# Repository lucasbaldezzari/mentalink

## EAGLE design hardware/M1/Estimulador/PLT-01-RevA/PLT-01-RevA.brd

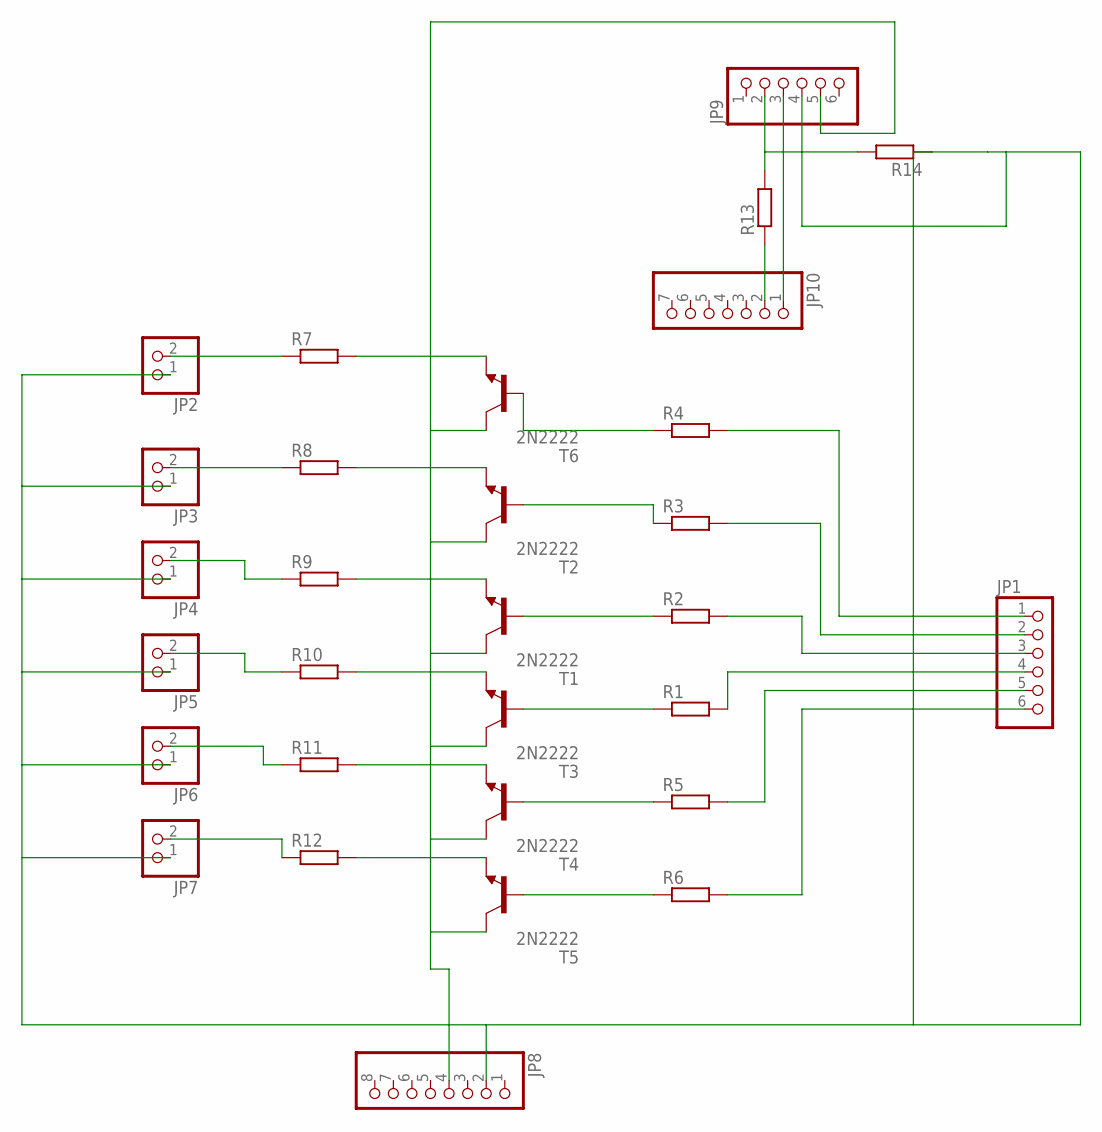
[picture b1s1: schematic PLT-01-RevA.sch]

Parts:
JP1, JP9: PINHD-1X6; 1X06
JP2, JP3, JP4, JP5, JP6, JP7: PINHD-1X2; 1X02
JP8: PINHD-1X8; 1X08
JP10: PINHD-1X7; 1X07
R1, R2, R3, R4, R5, R6, R7, R8, R9, R10, R11, R12, R13, R14: R-EU_0207/10; 0207/10
T1, T2, T3, T4, T5, T6: 2N2222; TO18

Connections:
GND: JP2.1, JP3.1, JP4.1, JP5.1, JP6.1, JP8.2, JP9.4, R14.1
unnamed: JP1.1, R4.2
unnamed: JP1.2, R3.2
unnamed: JP1.3, R2.2
unnamed: JP1.4, R1.2
unnamed: JP1.5, R5.2
unnamed: JP1.6, R6.2
unnamed: R6.1, T5.2 (B)
unnamed: R5.1, T4.2 (B)
unnamed: R1.1, T3.2 (B)
unnamed: R2.1, T1.2 (B)
unnamed: R3.1, T2.2 (B)
unnamed: R4.1, T6.2 (B)
unnamed: R7.2, T6.1 (E)
unnamed: JP2.2, R7.1
unnamed: R8.2, T2.1 (E)
unnamed: JP3.2, R8.1
unnamed: R9.2, T1.1 (E)
unnamed: JP4.2, R9.1
unnamed: R10.2, T3.1 (E)
unnamed: JP5.2, R10.1
unnamed: R11.2, T4.1 (E)
unnamed: JP6.2, R11.1
unnamed: R12.2, T5.1 (E)
unnamed: JP7.2, R12.1
unnamed: JP10.2, R13.1
unnamed: JP9.2, R13.2, R14.2
unnamed: JP9.3, JP10.1
unnamed: JP8.4, JP9.5, T1.3 (C), T2.3 (C), T3.3 (C), T4.3 (C), T5.3 (C), T6.3 (C)

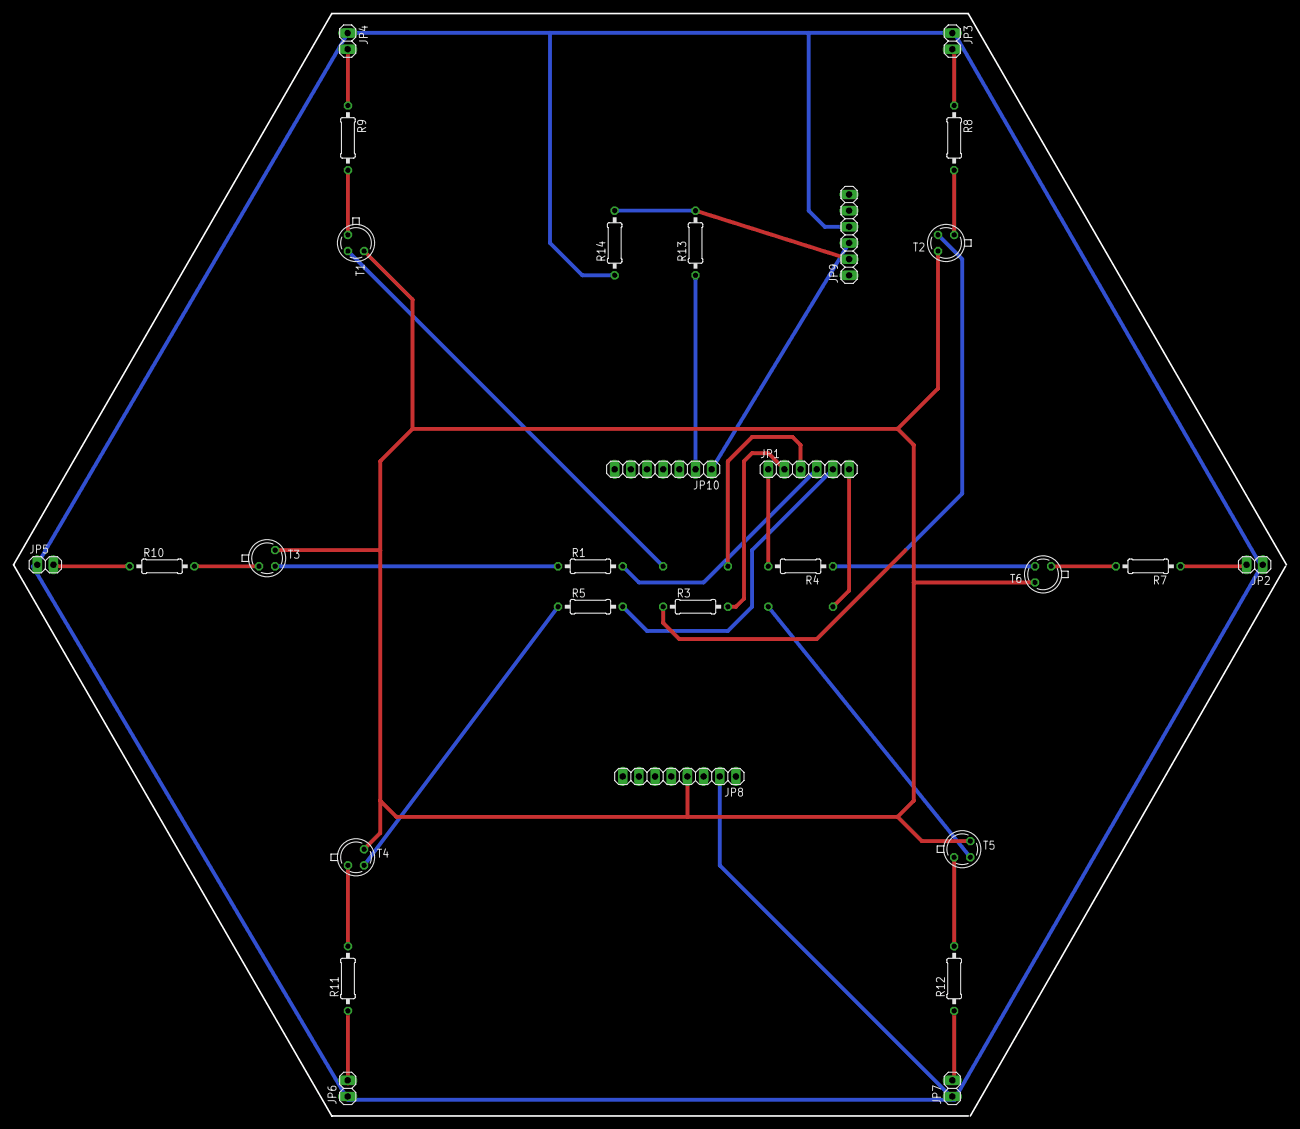
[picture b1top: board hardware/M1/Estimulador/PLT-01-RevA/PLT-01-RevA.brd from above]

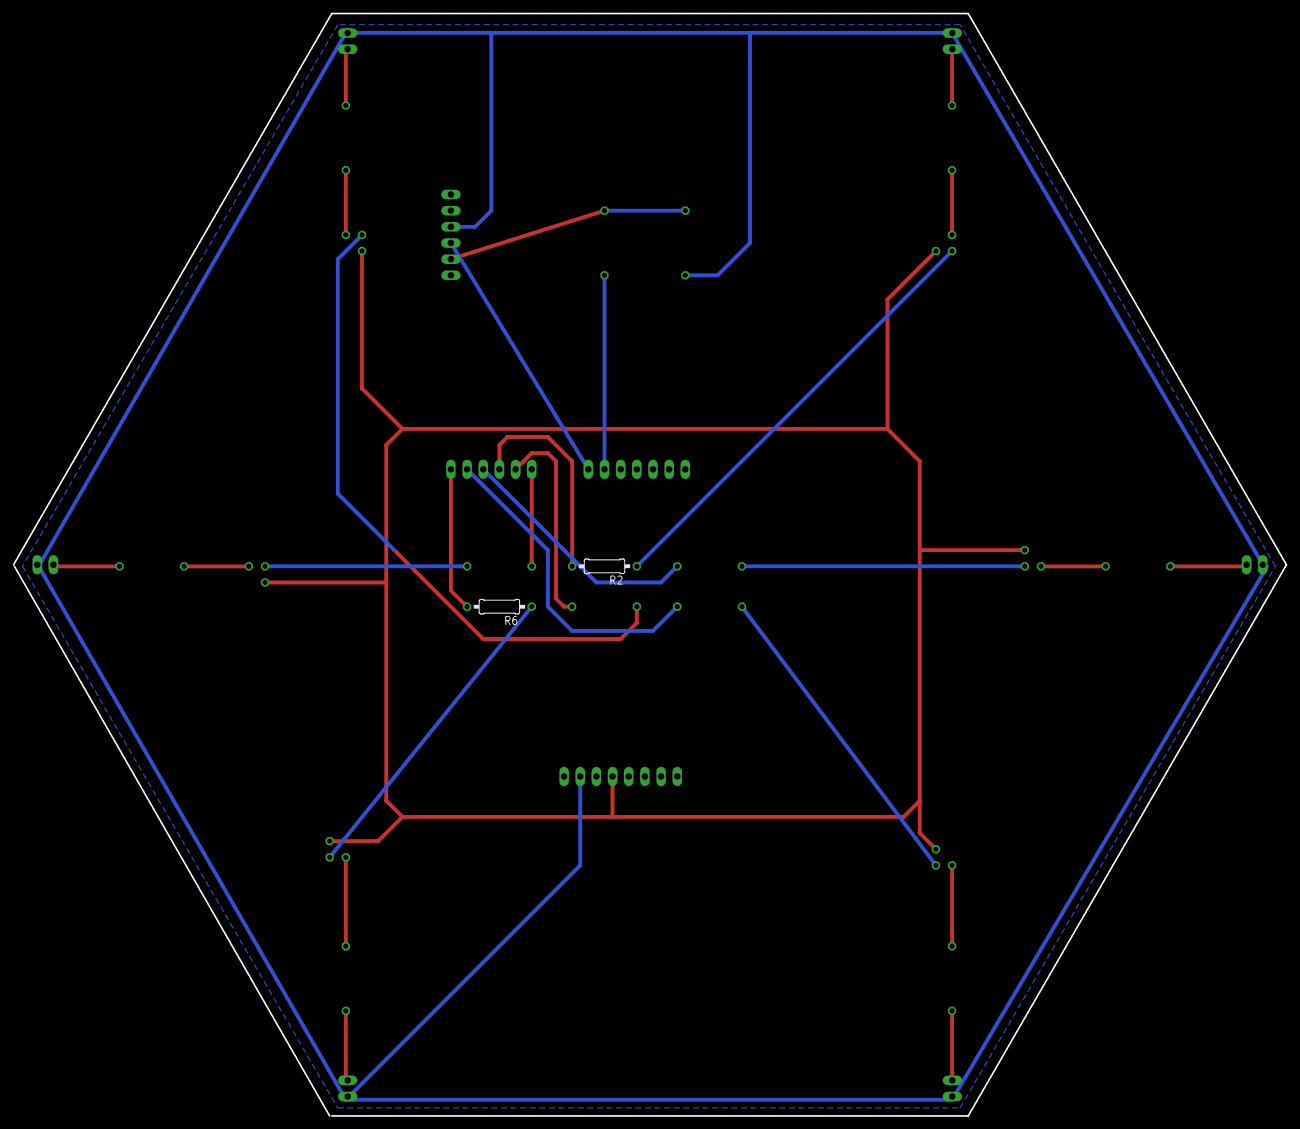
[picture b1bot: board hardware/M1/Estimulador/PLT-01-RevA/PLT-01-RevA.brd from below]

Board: 2 copper layers, 200.0 x 173.2 mm, 30 parts (2 on the bottom side), 29 nets.

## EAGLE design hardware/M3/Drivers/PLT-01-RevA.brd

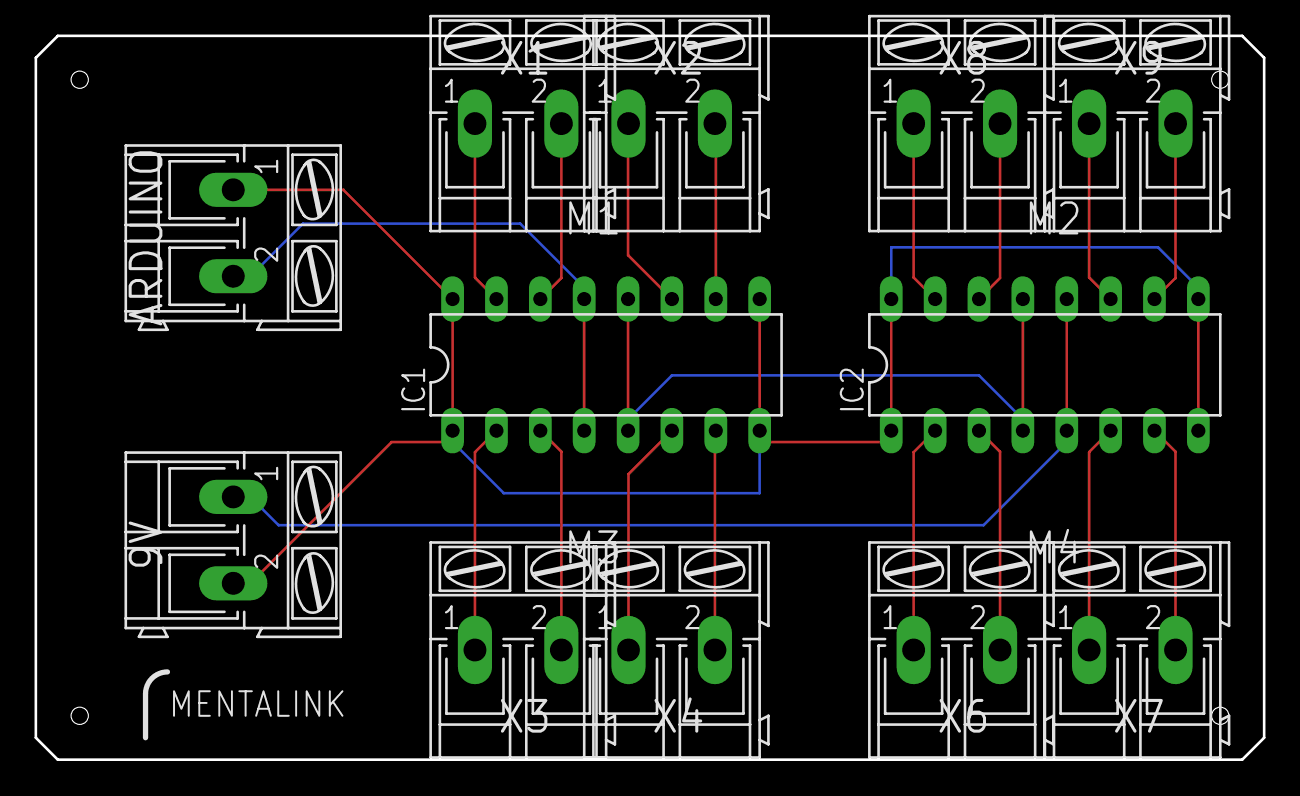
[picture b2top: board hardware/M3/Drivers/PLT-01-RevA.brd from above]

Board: 2 copper layers, 71.1 x 41.9 mm, 12 parts (0 on the bottom side), 20 nets.

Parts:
9V: AK300/2
ARDUINO: AK300/2
IC1, IC2: L293D; DIL16
X1, X2, X3, X4, X6, X7, X8, X9: AK300/2

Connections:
unnamed: IC1.15, X1.1
unnamed: IC1.14, X1.2
unnamed: IC1.11, X2.1
unnamed: IC1.10, X2.2
unnamed: IC1.2, X3.1
unnamed: IC1.3, X3.2
unnamed: IC1.6, X4.1
unnamed: IC1.7, X4.2
unnamed: IC2.2, X6.1
unnamed: IC2.3, X6.2
unnamed: IC2.6, X7.1
unnamed: IC2.7, X7.2
unnamed: IC2.10, X9.2
unnamed: IC2.11, X9.1
unnamed: IC2.15, X8.1
unnamed: IC2.14, X8.2
unnamed: 9V.2, ARDUINO.1, IC1.1, IC1.8, IC1.9, IC1.16, IC2.1, IC2.8, IC2.9, IC2.16
unnamed: ARDUINO.2, IC1.4, IC1.13
unnamed: 9V.1, IC2.5, IC2.12
unnamed: IC1.5, IC1.12, IC2.4, IC2.13

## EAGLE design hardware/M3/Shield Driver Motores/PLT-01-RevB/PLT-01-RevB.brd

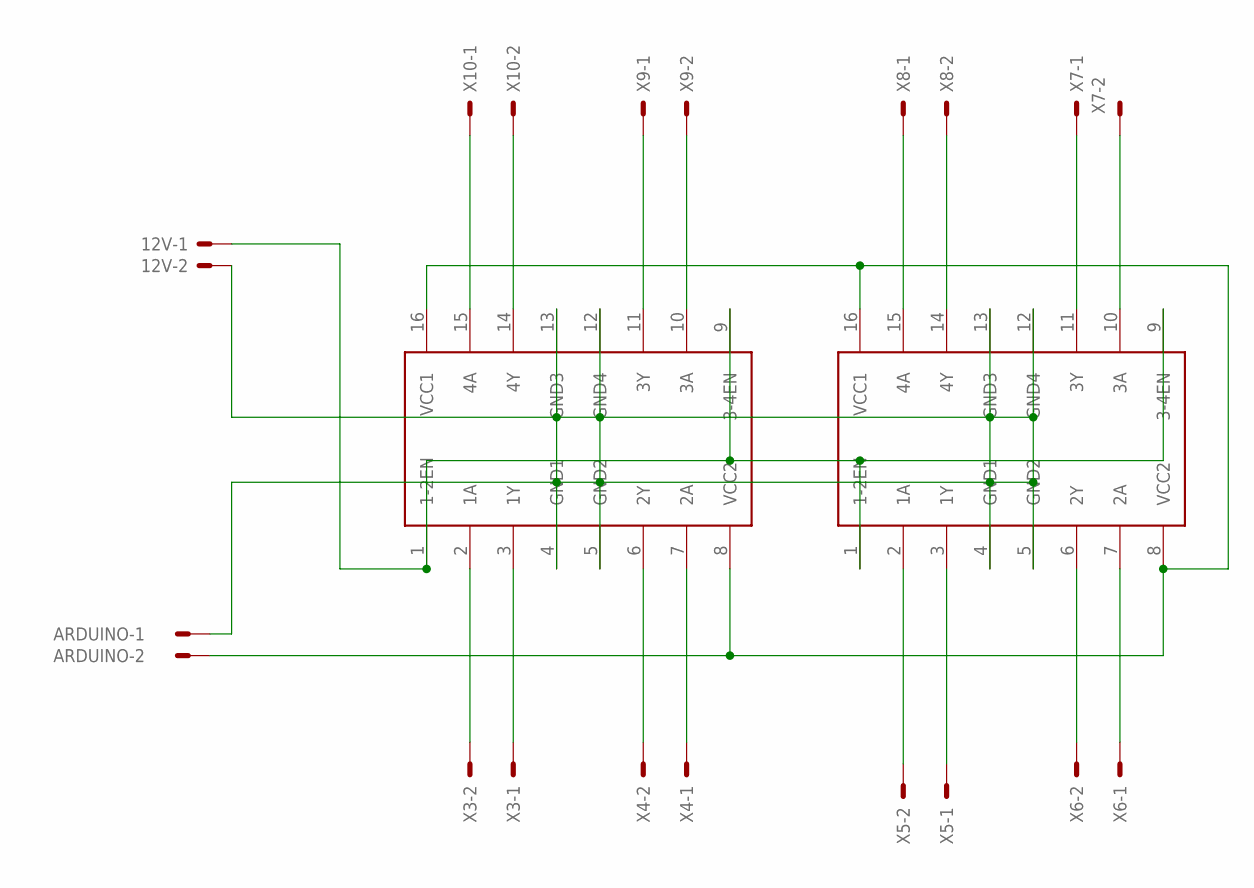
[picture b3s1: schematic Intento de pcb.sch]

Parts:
12V: 22-23-2021
ARDUINO: 22-23-2021
IC1, IC2: L293D; DIL16
X3, X4, X5, X6, X7, X8, X9, X10: 22-23-2021

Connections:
S$1: 12V.2, ARDUINO.1, IC1.4 (GND1), IC1.5 (GND2), IC1.12 (GND4), IC1.13 (GND3), IC2.4 (GND1), IC2.5 (GND2), IC2.12 (GND4), IC2.13 (GND3)
S$2: IC1.2 (1A), X3.2
S$3: IC1.3 (1Y), X3.1
S$4: IC1.6 (2Y), X4.2
S$5: IC1.7 (2A), X4.1
S$6: IC2.2 (1A), X5.2
S$7: IC2.3 (1Y), X5.1
S$8: IC2.6 (2Y), X6.2
S$9: IC2.7 (2A), X6.1
S$10: IC1.15 (4A), X10.1
S$11: IC1.14 (4Y), X10.2
S$12: IC1.11 (3Y), X9.1
S$13: IC1.10 (3A), X9.2
S$14: IC2.15 (4A), X8.1
S$15: IC2.14 (4Y), X8.2
S$16: IC2.11 (3Y), X7.1
S$17: IC2.10 (3A), X7.2
S$18: ARDUINO.2, IC1.8 (VCC2), IC1.16 (VCC1), IC2.8 (VCC2), IC2.16 (VCC1)
S$19: 12V.1, IC1.1 (1-2EN), IC1.9 (3-4EN), IC2.1 (1-2EN), IC2.9 (3-4EN)

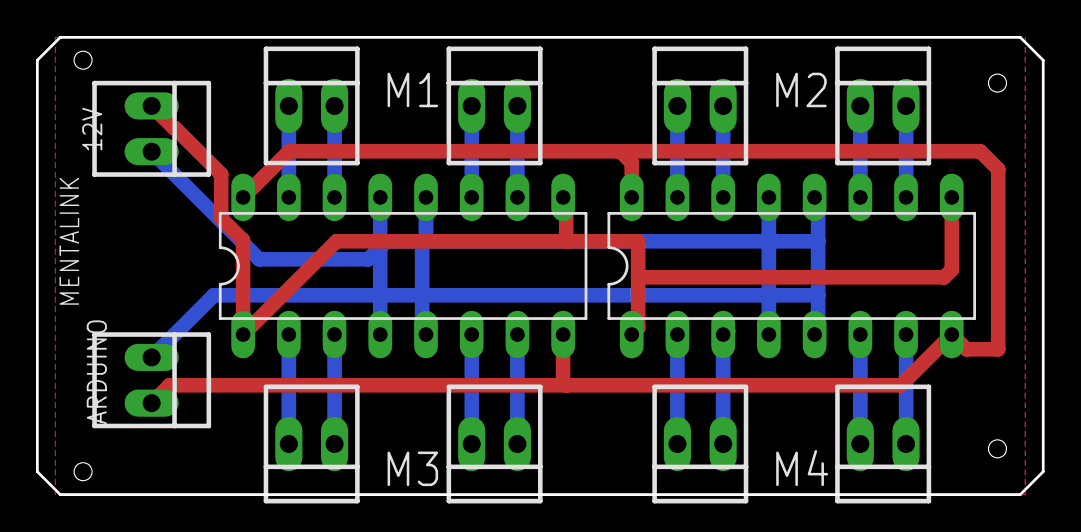
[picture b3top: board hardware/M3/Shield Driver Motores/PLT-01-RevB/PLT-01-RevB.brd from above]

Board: 2 copper layers, 55.9 x 25.4 mm, 12 parts (0 on the bottom side), 19 nets.

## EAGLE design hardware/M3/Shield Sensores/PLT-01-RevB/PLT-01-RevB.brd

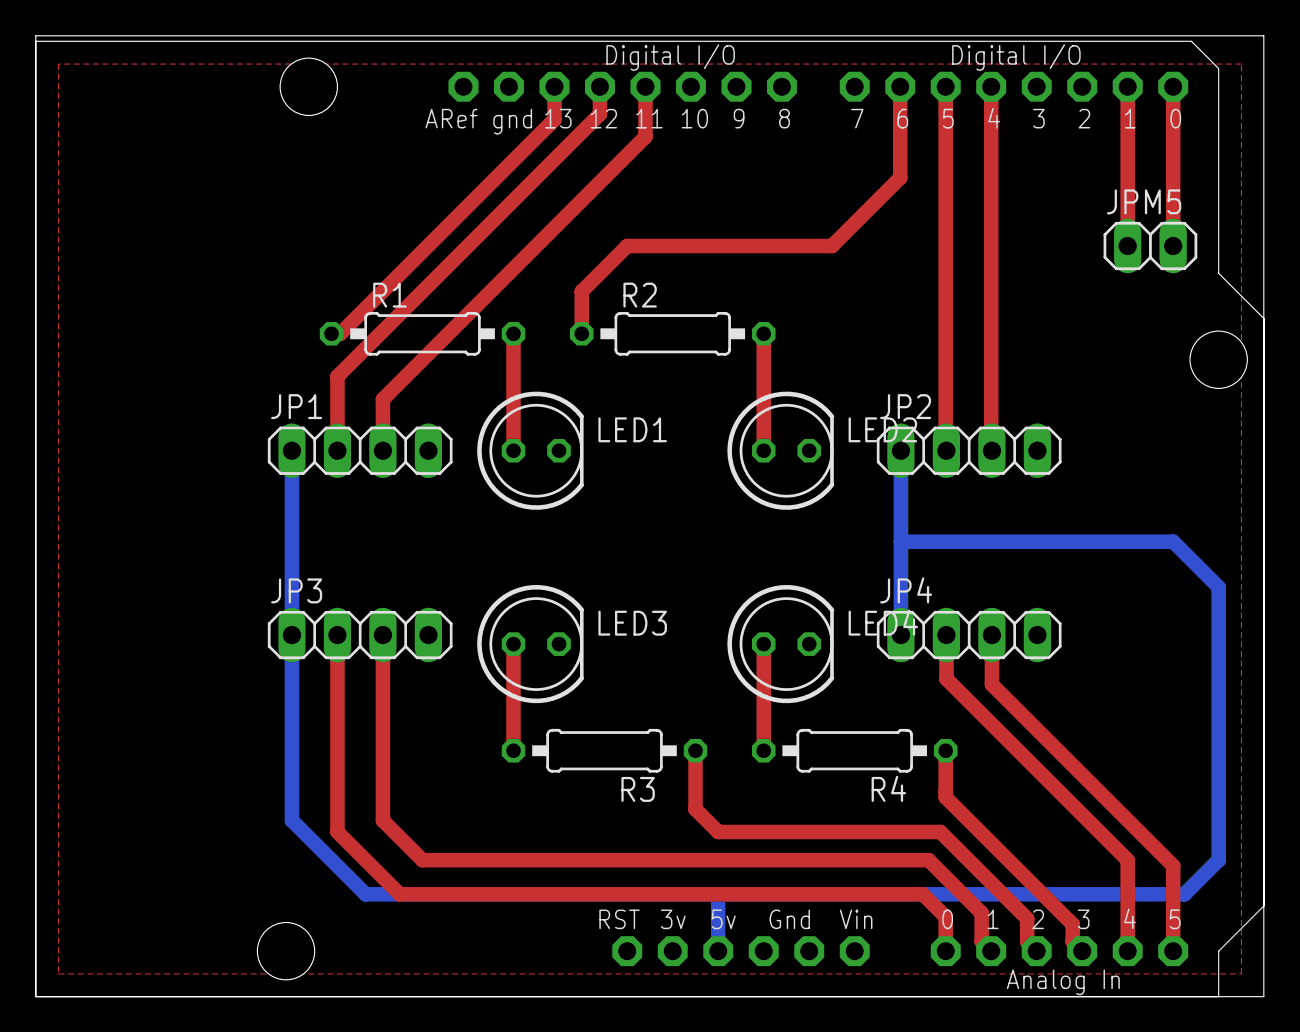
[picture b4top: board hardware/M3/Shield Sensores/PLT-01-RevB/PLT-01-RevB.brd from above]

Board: 2 copper layers, 68.6 x 53.6 mm, 14 parts (0 on the bottom side), 20 nets.

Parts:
JP1, JP2, JP3, JP4: 1X04
JPM5: 1X02
LED1, LED2, LED3, LED4: LED5MM
R1, R2, R3, R4: 0207/10
U$1: ARDUINOUNO; ARDUINO

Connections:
5V: JP1.1, JP2.1, JP3.1, JP4.1, U$1.5V
GND: JP1.4, JP2.4, JP3.4, JP4.4, LED1.K, LED2.K, LED3.K, LED4.K, U$1.GND, U$1.GND1, U$1.GND2
unnamed: R4.1, U$1.A3
unnamed: JP4.3, U$1.A5
unnamed: JP2.3, U$1.D4
unnamed: JP2.2, U$1.D5
unnamed: JP4.2, U$1.A4
unnamed: R3.1, U$1.A2
unnamed: JP1.3, U$1.D11
unnamed: JP1.2, U$1.D12
unnamed: R1.1, U$1.D13
unnamed: LED2.A, R2.2
unnamed: LED1.A, R1.2
unnamed: R2.1, U$1.D6
unnamed: LED4.A, R4.2
unnamed: JP3.2, U$1.A0
unnamed: LED3.A, R3.2
unnamed: JP3.3, U$1.A1
RX: JPM5.2, U$1.D0
TX: JPM5.1, U$1.D1
